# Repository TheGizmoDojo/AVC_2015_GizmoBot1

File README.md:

# AVC_2015_GizmoBot1
<p>Repository for AVC code.</p>

<p>This is the codebase for The Gizmo Dojo's 2015 Sparkfun AVC entry. Documentation will be sketchy,
but the basics should be here.</p>

<p>I've written the beginnings of a library for our very specific hardware setup. This is designed to prevent
damage to the control board.</p>

<p>The following commands can be used to move the car:</p>
<code>
init_movement();&nbsp;&nbsp;&nbsp;&nbsp;&nbsp;&nbsp;&nbsp;&nbsp;&nbsp;&nbsp;&nbsp;&nbsp;&nbsp;&nbsp;&nbsp;&nbsp;// Please call this at the beginning of setup().<br />
move_forward(time_in_ms);&nbsp;&nbsp;&nbsp;&nbsp;&nbsp;&nbsp;&nbsp;// This moves forward &lt;time_in_ms&gt; and coasts.<br />
move_forward_stop(time_in_ms);&nbsp;&nbsp;// This moves forward &lt;time_in_ms&gt; and stops.<br />
move_reverse(time_in_ms);&nbsp;&nbsp;&nbsp;&nbsp;&nbsp;&nbsp;&nbsp;// This moves backwards &lt;time_in_ms&gt; and coasts.<br />
move_reverse_stop(time_in_ms);&nbsp;&nbsp;// This moves backwards &lt;time_in_ms&gt; and stops.<br />
wheels_left();&nbsp;&nbsp;&nbsp;&nbsp;&nbsp;&nbsp;&nbsp;&nbsp;&nbsp;&nbsp;&nbsp;&nbsp;&nbsp;&nbsp;&nbsp;&nbsp;&nbsp;&nbsp;// This turns the wheels to the left position.<br />
wheels_right();&nbsp;&nbsp;&nbsp;&nbsp;&nbsp;&nbsp;&nbsp;&nbsp;&nbsp;&nbsp;&nbsp;&nbsp;&nbsp;&nbsp;&nbsp;&nbsp;&nbsp;// This turns the wheels to the right position.<br />
wheels_center();&nbsp;&nbsp;&nbsp;&nbsp;&nbsp;&nbsp;&nbsp;&nbsp;&nbsp;&nbsp;&nbsp;&nbsp;&nbsp;&nbsp;&nbsp;&nbsp;// This turns the wheels to the center (or straight) position.<br />
</code>
<br />&nbsp;<br />
More commands may be added if they are deemed useful.

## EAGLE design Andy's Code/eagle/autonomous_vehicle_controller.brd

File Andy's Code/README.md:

# autonomous_vehicle

Arduino source code for an autonomous vehicle using the following components:

1. Arduino Uno or Mega
2. Adafruit Ultimate GPS
3. Sparkfun HMC6352 magenetometer breakout
4. 5 x HC-SR04 ultra-sonic sensors
5. Pololu Qik 2s12v10 motor controller board

## Arduino Mega Notes

Need to replace standard SD library with this one that uses soft SPI on pins 10,11,12,13 instead of 50,51,52

https://github.com/adafruit/SD

| Arduino | Component   | Wire color |
|---------|-------------|------------|
| 10-13   | SD shield   | N/A        |
| 18      | GPS RX      | Gray       |
| 19      | GPS TX      | White      |
| 20      | Compass SDA | Gray       |
| 21      | Compass SCL | White      |
| 50      | Qik TX      | Gray       |
| 51      | Qik RX      | Purple     |
| 52      | Qik RESET   | White      |
| A8-A12  | HC-SR04     | Various    |

## Arduino Uno Notes (Untested)

Note that the GPS is connected to the hardware serial UART so cannot use serial monitor at the same time.

| Arduino | Component   | Wire color |
|---------|-------------|------------|
| 0       | GPS RX      | Gray       |
| 1       | GPS TX      | White      |
| 2       | Qik TX      | Gray       |
| 3       | Qik RX      | Purple     |
| 4       | Qik RESET   | White      |
| 10-13   | SD shield   | N/A        |
| A0-A3,7 | HC-SR04     | Various    |
| A4      | Compass SDA | Gray       |
| A5      | Compass SCL | White      |

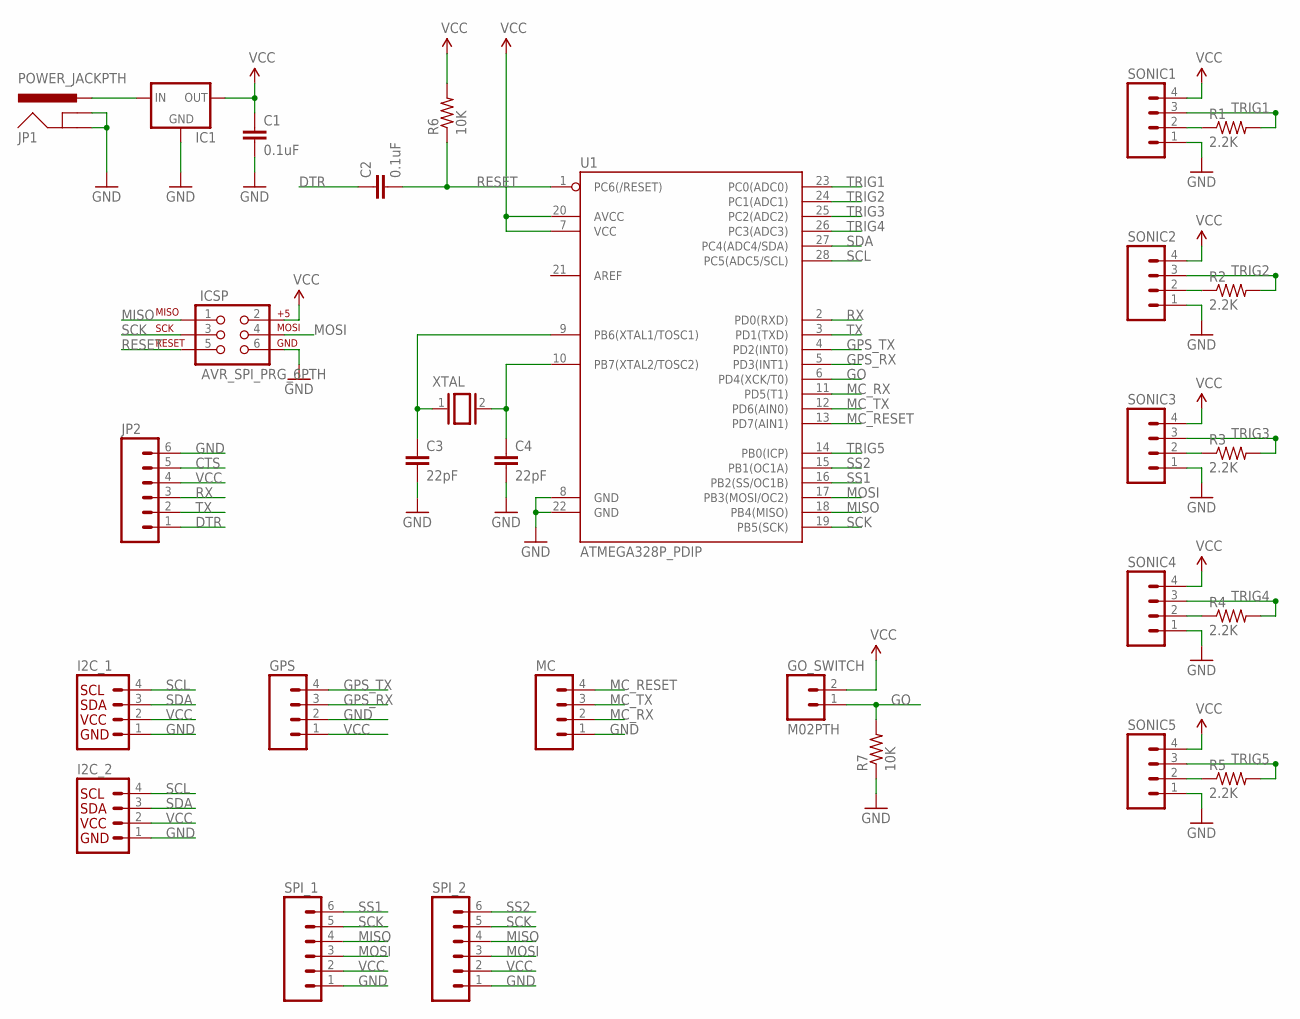
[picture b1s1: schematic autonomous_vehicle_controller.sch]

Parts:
C1, C2: 0.1uF; CAP-PTH-SMALL
C3, C4: 22pF; CAP-PTH-SMALL
GO_SWITCH: M02PTH; 1X02
GPS: M04PTH; 1X04
I2C_1, I2C_2: I2C_STANDARD; 1X04
IC1: V_REG_78XXSIDE; 78XXL
ICSP: AVR_SPI_PRG_6PTH; 2X3
JP1: POWER_JACKPTH; POWER_JACK_PTH
JP2: M06SILK_FEMALE_PTH; 1X06
MC: M04PTH; 1X04
R1, R2, R3, R4, R5: 2.2K; AXIAL-0.4
R6, R7: 10K; AXIAL-0.4
SONIC1, SONIC2, SONIC3, SONIC4, SONIC5: M04PTH; 1X04
SPI_1, SPI_2: M06SILK_FEMALE_PTH; 1X06
U1: ATMEGA328P_PDIP; DIL28-3
XTAL: XTAL/S; QS

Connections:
CTS: JP2.5
DTR: C2.1, JP2.1
GND: C1.2, C3.2, C4.2, GPS.2, I2C_1.1, I2C_2.1, IC1.GND, ICSP.6, JP1.GND, JP1.GNDBREAK, JP2.6, MC.1, R7.P$1 (1), SONIC1.1, SONIC2.1, SONIC3.1, SONIC4.1, SONIC5.1, SPI_1.1, SPI_2.1, U1.8 (GND), U1.22 (GND)
GO: GO_SWITCH.1, R7.P$2 (2), U1.6 (PD4(XCK/T0))
GPS_RX: GPS.3, U1.5 (PD3(INT1))
GPS_TX: GPS.4, U1.4 (PD2(INT0))
MC_RESET: MC.4, U1.13 (PD7(AIN1))
MC_RX: MC.2, U1.11 (PD5(T1))
MC_TX: MC.3, U1.12 (PD6(AIN0))
MISO: ICSP.1, SPI_1.4, SPI_2.4, U1.18 (PB4(MISO))
MOSI: ICSP.4, SPI_1.3, SPI_2.3, U1.17 (PB3(MOSI/OC2))
unnamed: IC1.IN, JP1.PWR
unnamed: C3.1, U1.9 (PB6(XTAL1/TOSC1)), XTAL.1
unnamed: R2.P$1 (1), SONIC2.2
unnamed: R1.P$1 (1), SONIC1.2
unnamed: R3.P$1 (1), SONIC3.2
unnamed: R4.P$1 (1), SONIC4.2
unnamed: R5.P$1 (1), SONIC5.2
unnamed: C4.1, U1.10 (PB7(XTAL2/TOSC2)), XTAL.2
RESET: C2.2, ICSP.5, R6.P$1 (1), U1.1 (PC6(/RESET))
RX: JP2.3, U1.2 (PD0(RXD))
SCK: ICSP.3, SPI_1.5, SPI_2.5, U1.19 (PB5(SCK))
SCL: I2C_1.4, I2C_2.4, U1.28 (PC5(ADC5/SCL))
SDA: I2C_1.3, I2C_2.3, U1.27 (PC4(ADC4/SDA))
SS1: SPI_1.6, U1.16 (PB2(SS/OC1B))
SS2: SPI_2.6, U1.15 (PB1(OC1A))
TRIG1: R1.P$2 (2), SONIC1.3, U1.23 (PC0(ADC0))
TRIG2: R2.P$2 (2), SONIC2.3, U1.24 (PC1(ADC1))
TRIG3: R3.P$2 (2), SONIC3.3, U1.25 (PC2(ADC2))
TRIG4: R4.P$2 (2), SONIC4.3, U1.26 (PC3(ADC3))
TRIG5: R5.P$2 (2), SONIC5.3, U1.14 (PB0(ICP))
TX: JP2.2, U1.3 (PD1(TXD))
VCC: C1.1, GO_SWITCH.2, GPS.1, I2C_1.2, I2C_2.2, IC1.OUT, ICSP.2, JP2.4, R6.P$2 (2), SONIC1.4, SONIC2.4, SONIC3.4, SONIC4.4, SONIC5.4, SPI_1.2, SPI_2.2, U1.7 (VCC), U1.20 (AVCC)

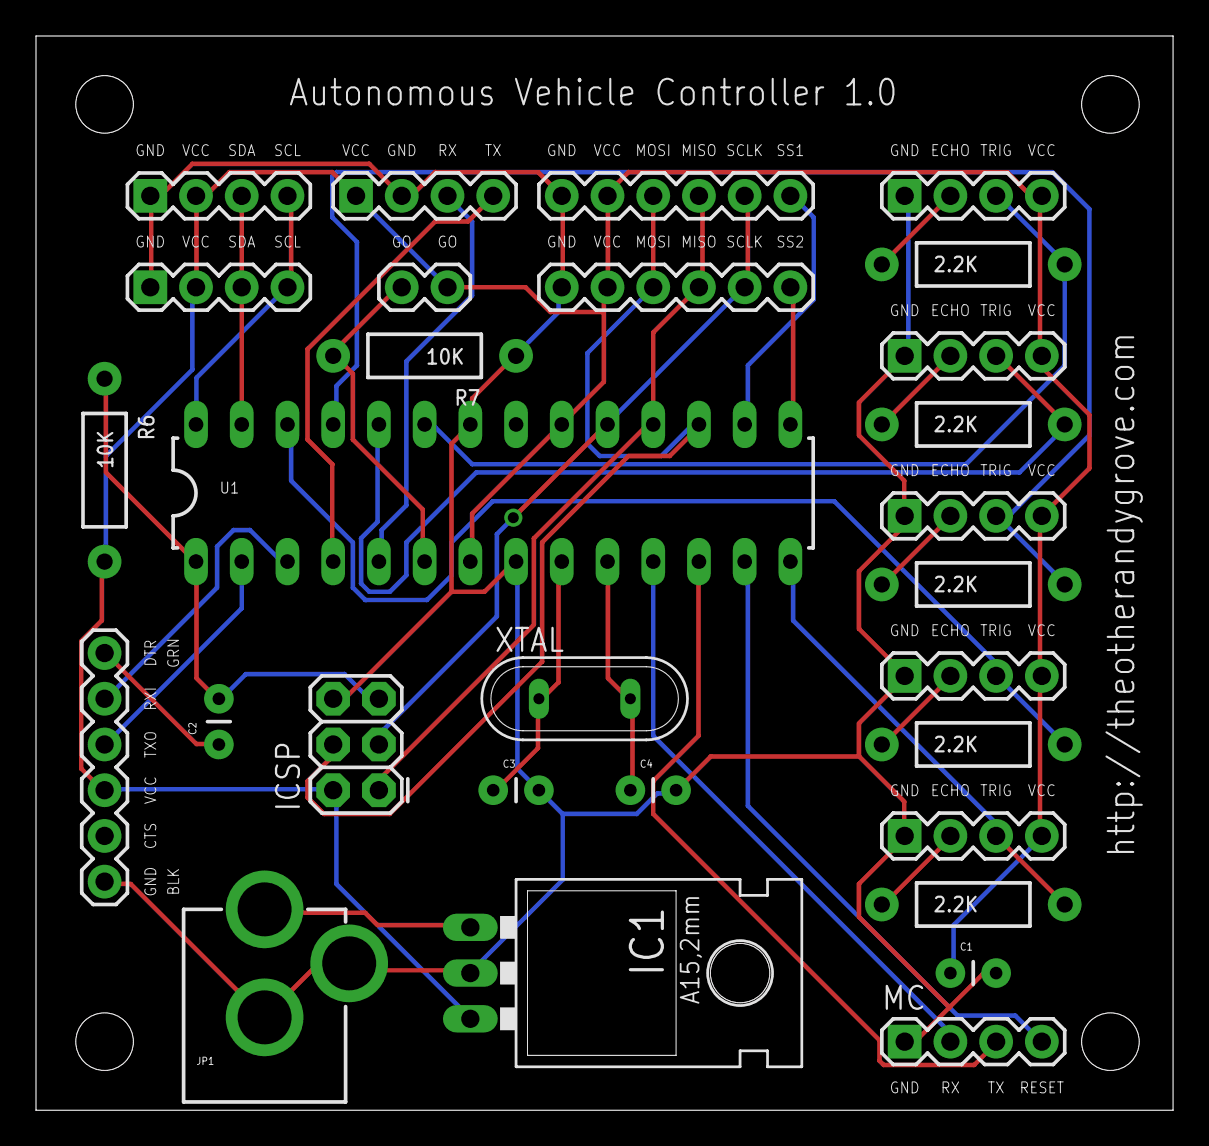
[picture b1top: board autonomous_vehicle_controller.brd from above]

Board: 2 copper layers, 63.2 x 59.7 mm, 29 parts (0 on the bottom side), 32 nets.

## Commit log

2015-05-20 Initial cloning of codebase
2015-05-20 Adding Andy's Code
2015-05-26 Update GizmoBot1.ino
    Added init GPS from Andy's code
2015-05-26 Create GizmoBot1Untested
2015-05-31 Update GizmoBot1Untested
    Added more of anys code, GPS.
2015-06-06 Integrate GPS and Compass into Andy's codebase
    We integrated the GPS and Compass functionality into Andy’s code. The
    movement library is in place, but the code hasn’t been adjusted to use
    the proper movement for our rack and pinion steering.
2015-06-06 GPS and Compass
    Added GPS and Compass support to Andy’s codebase (and switched to
    Andy’s codebase). Still need movement stuff fixed. GPS doesn’t seem to
    update with movement, so need to fix that.
2015-06-19 Update GizmoBot1.ino
    Toms Updates
2015-06-19 Delete GizmoBot1Untested
    Deleting this file, untested file
2015-06-19 Toms updates
    Toms updates
2018-08-07 Loosely labeled as v1.5, code from end of 2016
2018-08-07 Loosely labeled as v1.6, code from beginning of 2017
2018-08-07 loosely versioned as v1.7, code from end of 2017
    Sorry for the ugly code...
2018-08-07 Some of these libraries are necessary for code.
2018-08-21 Start adding code to calculate heading based on wheel encoders
    It's working for turns in one direction, but not another. See tests.
2018-08-24 Started restruction code into logical classes
2018-08-24 Fix wheel encoder heading calculations
2018-08-24 Fix compilation in Arduino IDE
2018-08-24 Use radians to make calculations faster
2018-08-24 Fix broken test
2018-08-24 Added Vec2d class for basic point math functions
2018-08-30 Added wheel encoder positioning/heading logic
2018-08-31 Move point code into gizmobot
2018-08-31 Fix some C++ stuff; add units to variables
2018-08-31 wheel encoder + waypoint navigation logic
2018-09-01 wheel encoder & testing basic waypoints
2018-09-01 Added code to run on 9df imu
2018-09-04 Added files via upload
    Includes changes for goPin (switch to make it go), and gizmobot will drive forward for about 1 second before allowing any turning.
2018-09-05 Changed the startup code, dialed in center orientation for wheels, other small changes.
2018-09-05 trying to intigrate gps data
2018-09-05 Progress on gps intigration
2018-09-06 Update the tick count for new encoder pattern
2018-09-06 Update steering values for new servo horn
2018-09-06 Remove scaling of wheel encoder reading cutoff
    I was getting bad readings, so just revert to the old cutoff
2018-09-07 Speedier bot, modified filter accordingly, pushing so we don't lose this commit specifically
2018-09-07 Rely on GPS more
    It's navigating to waypoints pretty well!
2018-09-07 added compass, updated wheel encoder to use same radians/x,y as gps
2018-09-07 attempting to fix coordinate system
2018-09-07 Revert "attempting to fix coordinate system"
    This reverts commit a56d286e8033b435c01a796edc88ac6ad9473555.
2018-09-07 Revert "added compass, updated wheel encoder to use same radians/x,y as gps"
    This reverts commit 98856396aa2226bd38e003b449ad09e2a052b89f.
2018-09-07 added compass and fixed coordinate system
2018-09-08 Adding Sparkfun VL53L1X TOF sensor library.
2018-09-08 0.25% drift error correction
    The drift seems to have stopped, scaled one of the wheel ticks by 1.0025
2018-09-08 Code added for 3 TOF distance sensors
2018-09-08 Pulling in Taylor's waypoint conversion routine

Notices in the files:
parts and their libraries:
SparkFun-Capacitors: Licensing: Creative Commons ShareAlike 4.0 International - https://creativecommons.org/licenses/by-sa/4.0
